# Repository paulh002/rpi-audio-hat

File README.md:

# rpi-audio-hat
Raspberry Pi PCM1808 and 5102 audio hat for SDR tranceiver.
This board can be used with the Tayloe mixers in this repo https://github.com/paulh002/SoapyHifiBerry as alternative for the HifiBerry
The SoapyHifiBerry driver is used to supply IQ signals to the SDR software see sdrberry SDR software (https://github.com/paulh002/sdrberry)
Configure the SoapyHifiBerry config file with the correct audio board name and sample frequencey

To test the board:
- To check if board is loaded:
```
aplay -l 
arecord -l
```

- Reord and play:
```
arecord -D hw:0,1 -c 2 -f S24_LE -r 96000 test.wav
aplay -c2 -f S24_LE -r 96000 test.wav
```

## Hardware
Kicad files and gerbers are availeble in hardware directory.
R10 and R11 are used to switch between clock from the Pi or internal PLL of the pcm5102 (gnd is internal pll)
J5 exposes I2S for setting the mixer frequency of the si5351 on the Tayloe mixer board.

## Prototype
Picture shows prototype using cheep aliexpress adc and dac boards
To connect the boards you can use this table:

pcm 5102
| Board | GPIO | Pin |
| ----- | ---- | --- |
| SCK   |  4   |  12 | // or connect to gnd
| LCK   | 19   |  35 |
| BCK   | 18   |  12 |
| DIN   | 21   |  40 |
| 5V    | 5V   |   2 |
| FMT   | GND  |  19 |
| FLT   | GND  |  19 |
| XSMT  | 3v   |   1 |

pcm 1808
| Board| GPIO | Pin |
| ---- | ---- | --- |
| SCK  |  4   |  12 | // or connect to gnd
| LCK  | 19   |  35 |
| BCK  | 18   |  12 |
| Dout | 20   |  38 |
| MD0  | 3V   |   1 |
| MD1  | 3V   |   1 |
| 5V   | 5V   |   2 |
| 3V   | 3V   |   1 |
| SCLK |  4   |   7 |  // SCLK need a clock, this can be generated by raspberry pi (See PiClock) but better is to use an xtal oscillator 24.576 Mhz for 96 Khz or 49.125 to overclock to 196 Khz

## Kicad files
Kicad design is a pcb version of the audio board

## How compile and install driver for pcm1808 and pcm5102
To support the audio card in slave mode an overlay need to be created. The raspberry pi supports already most audio cards with pcm1808 and pcm5102.
The procedure and files are taken from Akiyuki Okayasu github page https://github.com/AkiyukiOkayasu/RaspberryPi_I2S_Slave

Compile on Raspberry Pi  
```bash
dtc -@ -H epapr -O dtb -o genericstereoaudiocodec.dtbo -Wno-unit_address_vs_reg genericstereoaudiocodec.dts
```

Copy genericstereoaudiocodec.dtbo to /boot/overlays  
```bash
sudo cp genericstereoaudiocodec.dtbo /boot/overlays
```

Edit /boot/config.txt  
Enable I2S and add genericstereoaudiocodec device tree overlay  
```/boot/config.txt    # Uncomment some or all of these to enable the optional hardware interface
#dtparam=i2c_arm=on
dtparam=i2s=on
#dtparam=spi=on
dtoverlay=genericstereoaudiocodec
```

If you don't need HDMI audio output and Raspberry Pi's headphone output, comment out "dtparam=audio=on" by hash.  
like this.  
```/boot/config.txt
#dtparam=audio=on
```

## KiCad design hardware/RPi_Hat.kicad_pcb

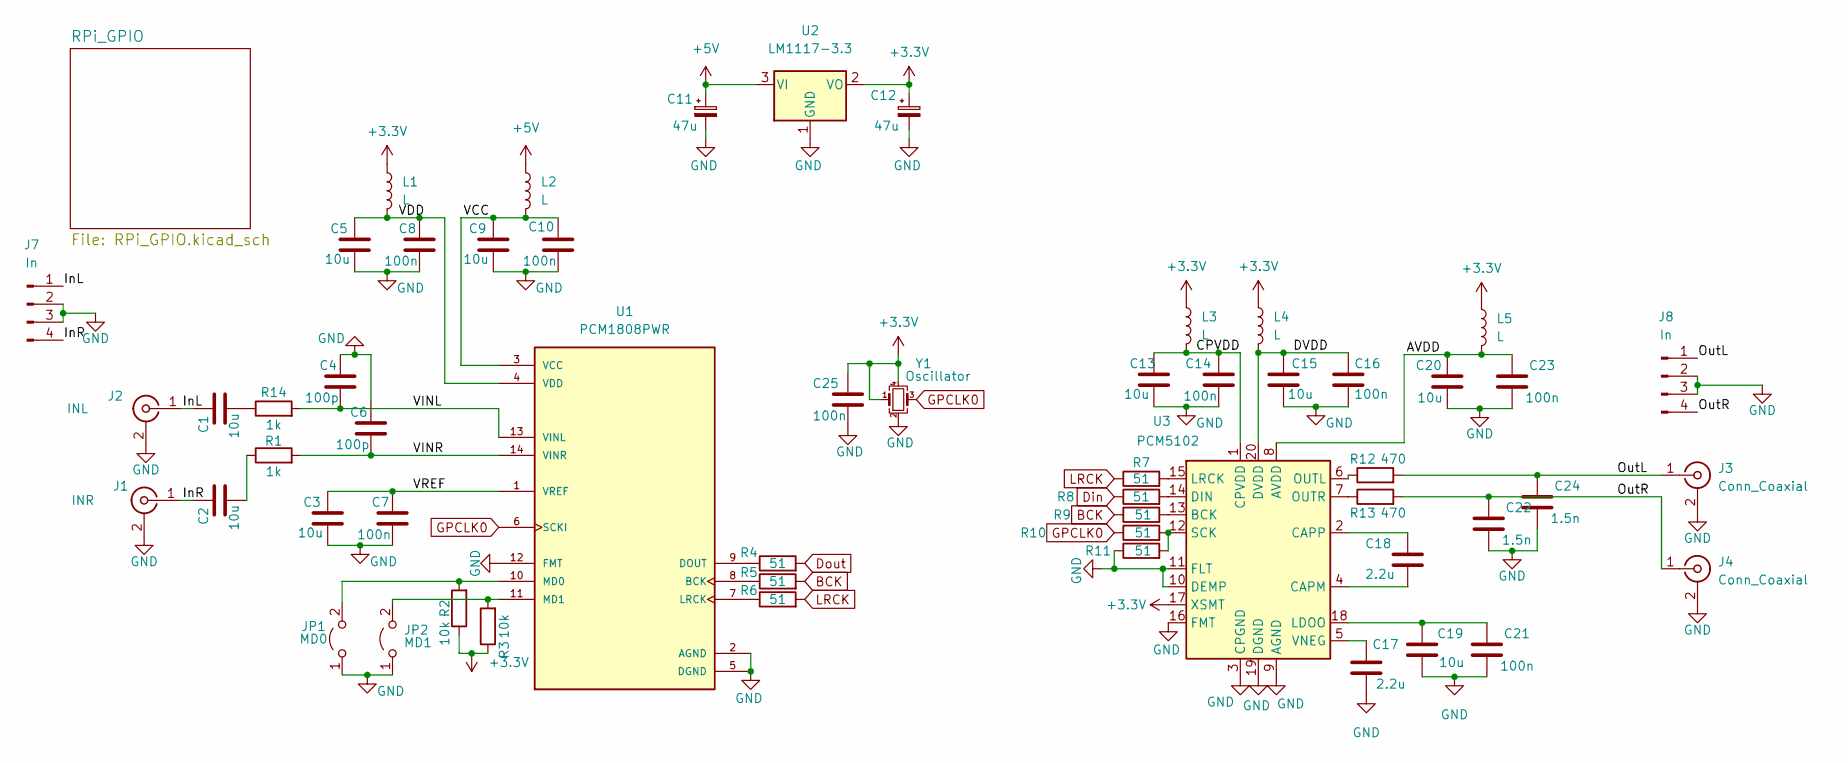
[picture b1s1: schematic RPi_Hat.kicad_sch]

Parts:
C1, C2, C3, C5, C9, C13, C15, C19, C20: 10u; C_0805_2012Metric
C4, C6: 100p; C_0805_2012Metric
C7, C8, C10, C14, C16, C21, C23, C25: 100n; C_0805_2012Metric
C11, C12: 47u; C_Radial_D5.0mm_H7.0mm_P2.00mm
C17, C18: 2.2u; C_0805_2012Metric
C22, C24: 1.5n; C_0805_2012Metric
J1: INR; SMA_Amphenol_132134_Vertical
J2: INL; SMA_Amphenol_132134_Vertical
J3, J4: Conn_Coaxial; SMA_Amphenol_132134_Vertical
J7, J8: In; PinHeader_1x04_P2.54mm_Vertical
JP1: MD0; SolderJumper-2_P1.3mm_Open_Pad1.0x1.5mm
JP2: MD1; SolderJumper-2_P1.3mm_Open_Pad1.0x1.5mm
L1, L2, L3, L4, L5: L; R_0603_1608Metric
R1, R14: 1k; R_0805_2012Metric
R2, R3: 10k; R_0805_2012Metric
R4, R5, R6, R7, R8, R9, R10, R11: 51; R_0805_2012Metric
R12, R13: 470; R_0805_2012Metric
U1: PCM1808PWR; SOP65P640X120-14N; PARTREV B
U2: LM1117-3.3; SOT-223-3_TabPin2
U3: PCM5102; TSSOP-20_4.4x6.5mm_P0.65mm
Y1: Oscillator; Crystal_SMD_3225-4Pin_3.2x2.5mm

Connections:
+3.3V: C12.1, C25.1, L1.1, L3.1, L4.1, L5.1, R2.1, R3.1, U2.2 (VO), U3.17 (XSMT), Y1.1, Y1.4
+5V: C11.1, L2.1, U2.3 (VI); also elsewhere on the board
/AVDD: C20.1, C23.1, L5.2, U3.8 (AVDD)
/CPVDD: C13.1, C14.1, L3.2, U3.1 (CPVDD)
/DVDD: C15.1, C16.1, L4.2, U3.20 (DVDD)
/InL: C1.1, J2.1 (In), J7.1
/InR: C2.1, J1.1 (In), J7.4
/OutL: C24.1, J3.1 (In), J8.1, R12.2
/OutR: C22.1, J4.1 (In), J8.4, R13.2
/VCC: C9.1, C10.1, L2.2, U1.3 (VCC)
/VDD: C5.1, C8.1, L1.2, U1.4 (VDD)
/VINL: C4.2, R14.2, U1.13 (VINL)
/VINR: C6.2, R1.2, U1.14 (VINR)
/VREF: C3.1, C7.1, U1.1 (VREF)
BCK: R5.2, R9.1; also elsewhere on the board
Din: R8.1; also elsewhere on the board
Dout: R4.2; also elsewhere on the board
GND: C3.2, C4.1, C5.2, C6.1, C7.2, C8.2, C9.2, C10.2, C11.2, C12.2, C13.2, C14.2, C15.2, C16.2, C17.2, C19.2, C20.2, C21.2, C22.2, C23.2, C24.2, C25.2, J1.2 (Ext), J2.2 (Ext), J3.2 (Ext), J4.2 (Ext), J7.2, J7.3, J8.2, J8.3, JP1.1 (A), JP2.1 (A), R11.1, U1.2 (AGND), U1.5 (DGND), U1.12 (FMT), U2.1 (GND), U3.3 (CPGND), U3.9 (AGND), U3.10 (DEMP), U3.11 (FLT), U3.16 (FMT), U3.19 (DGND), Y1.2; also elsewhere on the board
GPCLK0: R10.1, U1.6 (SCKI), Y1.3; also elsewhere on the board
LRCK: R6.2, R7.1; also elsewhere on the board
unnamed: C1.2, R14.1
unnamed: C2.2, R1.1
unnamed: C17.1, U3.5 (VNEG)
unnamed: C18.1, U3.2 (CAPP)
unnamed: C18.2, U3.4 (CAPM)
unnamed: C19.1, C21.1, U3.18 (LDOO)
unnamed: JP1.2 (B), R2.2, U1.10 (MD0)
unnamed: JP2.2 (B), R3.2, U1.11 (MD1)
unnamed: R4.1, U1.9 (DOUT)
unnamed: R5.1, U1.8 (BCK)
unnamed: R6.1, U1.7 (LRCK)
unnamed: R7.2, U3.15 (LRCK)
unnamed: R8.2, U3.14 (DIN)
unnamed: R9.2, U3.13 (BCK)
unnamed: R10.2, R11.2, U3.12 (SCK)
unnamed: R12.1, U3.6 (OUTL)
unnamed: R13.1, U3.7 (OUTR)

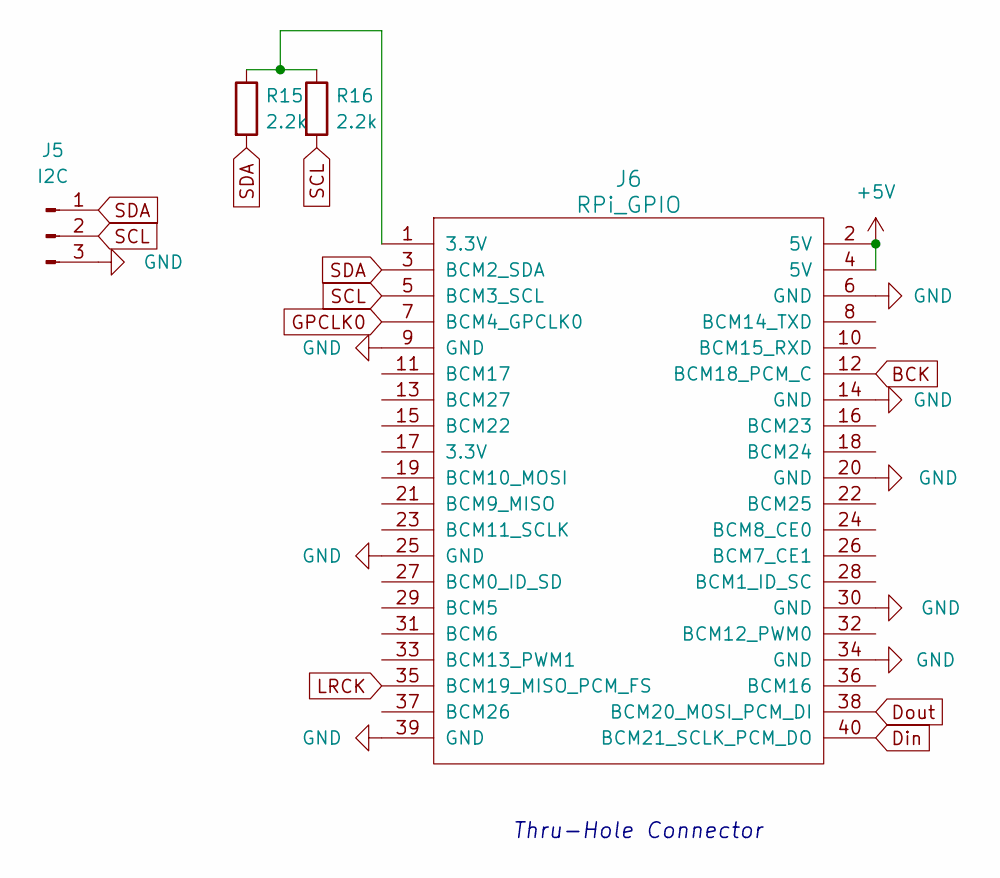
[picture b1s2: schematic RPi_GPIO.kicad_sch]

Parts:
J5: I2C; PinHeader_1x03_P2.54mm_Vertical
J6: RPi_GPIO; Pin_Header_Straight_2x20
R15, R16: 2.2k; R_0805_2012Metric

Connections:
+5V: J6.2 (5V), J6.4 (5V); also elsewhere on the board
BCK: J6.12 (BCM18_PCM_C); also elsewhere on the board
Din: J6.40 (BCM21_SCLK_PCM_DO); also elsewhere on the board
Dout: J6.38 (BCM20_MOSI_PCM_DI); also elsewhere on the board
GND: J5.3, J6.6 (GND), J6.9 (GND), J6.14 (GND), J6.20 (GND), J6.25 (GND), J6.30 (GND), J6.34 (GND), J6.39 (GND); also elsewhere on the board
GPCLK0: J6.7 (BCM4_GPCLK0); also elsewhere on the board
LRCK: J6.35 (BCM19_MISO_PCM_FS); also elsewhere on the board
unnamed: J6.1 (3.3V), R15.1, R16.1
SCL: J5.2, J6.5 (BCM3_SCL), R16.2
SDA: J5.1, J6.3 (BCM2_SDA), R15.2

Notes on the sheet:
Thru-Hole Connector

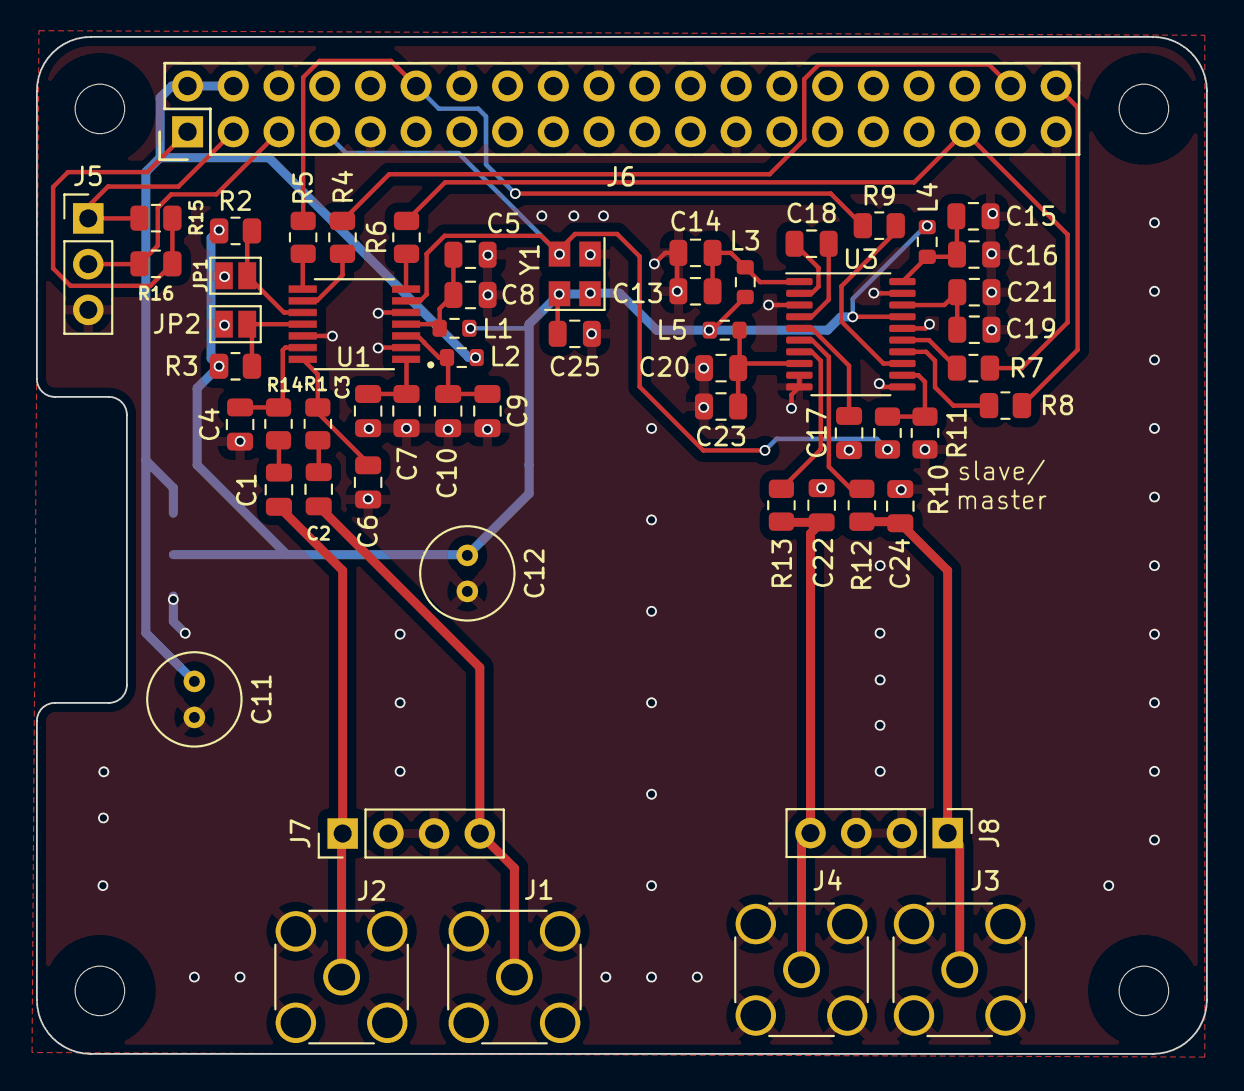
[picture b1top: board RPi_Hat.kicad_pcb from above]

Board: 4 copper layers, 65.0 x 56.5 mm, 60 parts (1 on the bottom side), 40 nets.
